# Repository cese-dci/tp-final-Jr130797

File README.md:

## Trabajo práctico final de la asignatura DCI ##

Este repositorio contiene el trabajo práctico final para la asignatura de Diseño de Circuitos Impresos de la carrera de posgrado de FIUBA.

* Autor: Ivan Vargas Marza 
* Título corto del trabajo:  Réplica de adaptador de amplificador Adafruit I2S Clase D
* Descripción: Se realiza la réplica del adaptador indicado, cambiando en modo mono del mismo a estéreo 

## Licencia de este trabajo ##

La licencia para este trabajo es la de Creative Commons Attribution-ShareAlike 4.0 International (CC BY-SA 4.0)

Se puede conocer más a detalle esta licencia en el siguiente enlace: https://creativecommons.org/licenses/by-sa/4.0/

## Estructura del TP FINAL ##

Toda la información pertinente a la réplica que se realizará se encuentra en: https://www.adafruit.com/product/3006

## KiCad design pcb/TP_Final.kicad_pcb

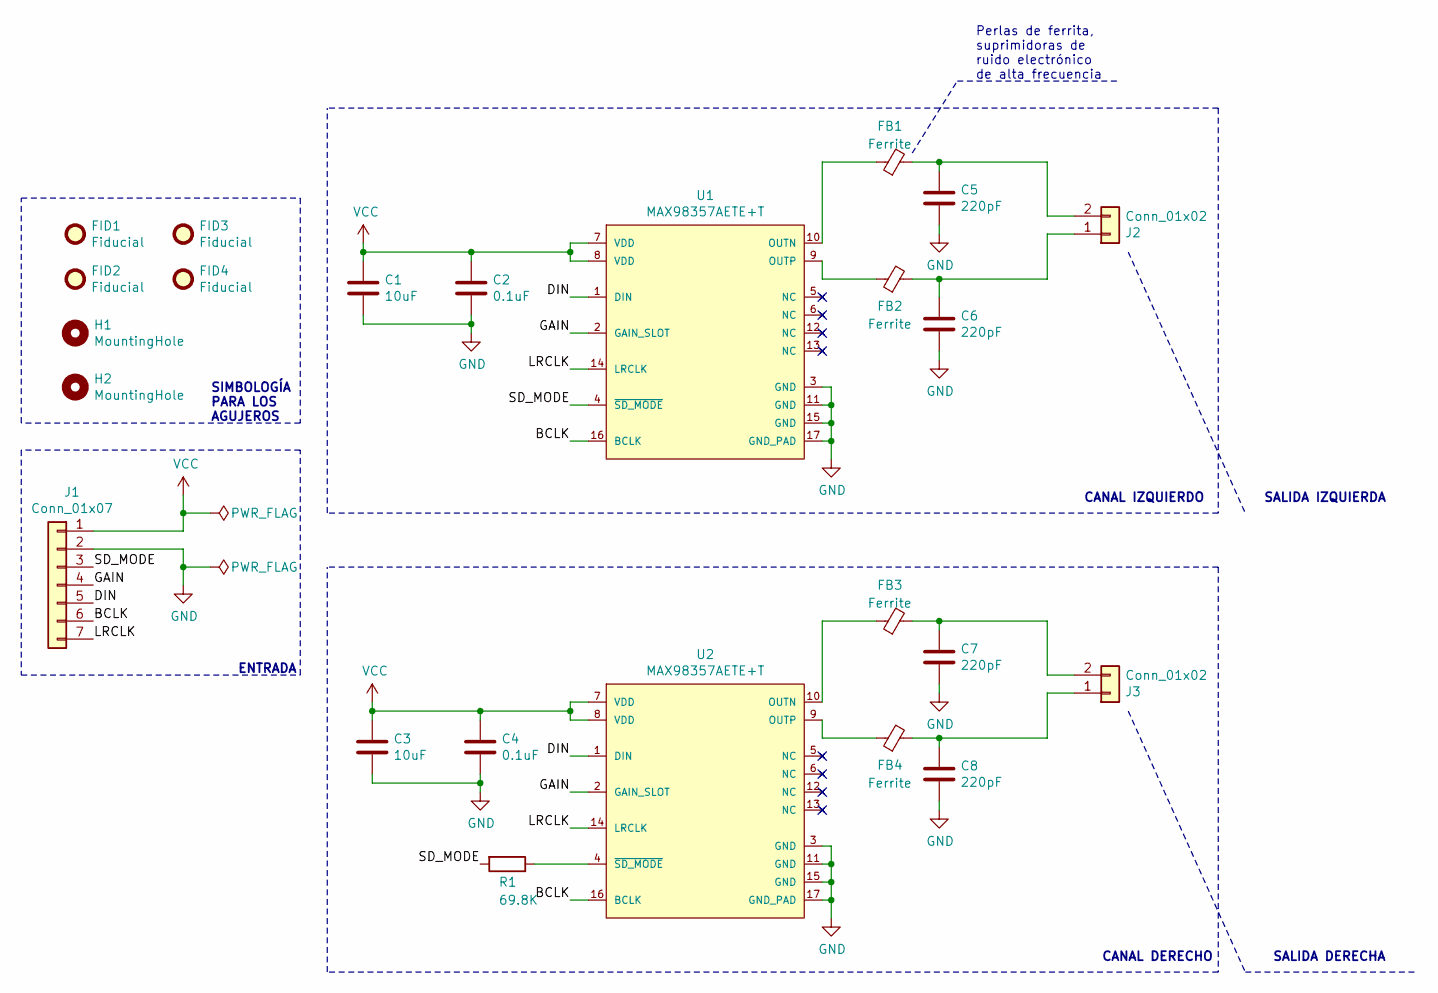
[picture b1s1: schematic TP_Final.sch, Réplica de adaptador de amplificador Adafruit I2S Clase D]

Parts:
C1, C3: 10uF; C_0805_2012Metric
C2, C4: 0.1uF; C_0805_2012Metric
C5, C6, C7, C8: 220pF; C_0805_2012Metric
FB1, FB2, FB3, FB4: Ferrite; Fuse_0805_2012Metric; digikey part number 710-742792030
FID1, FID2, FID3, FID4: Fiducial; Fiducial_0.5mm_Mask1mm
H1, H2: MountingHole; MountingHole_2mm
J1: Conn_01x07; PinHeader_1x07_P2.54mm_Vertical
J2, J3: Conn_01x02; TerminalBlock_Phoenix_MPT-0,5-2-2.54_1x02_P2.54mm_Horizontal
R1: 69.8K; R_0805_2012Metric; digikey description Resistores de alta frecuencia RF
U1, U2: MAX98357AETE+T; Maxim_Electronics-21-0896-0-0-0; mouser part number 700-MAX98357AETE+T; digikey description Amplifier IC 2-Channel (Stereo) Class D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

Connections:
/BCLK: J1.6, U1.16 (BCLK), U2.16 (BCLK)
/DIN: J1.5, U1.1 (DIN), U2.1 (DIN)
/GAIN: J1.4, U1.2 (GAIN_SLOT), U2.2 (GAIN_SLOT)
/LRCLK: J1.7, U1.14 (LRCLK), U2.14 (LRCLK)
/SD_MODE: J1.3, R1.2, U1.4 (~SD_MODE~)
GND: C1.2, C2.2, C3.2, C4.2, C5.2, C6.2, C7.2, C8.2, J1.2, U1.3 (GND), U1.11 (GND), U1.15 (GND), U1.17 (GND_PAD), U2.3 (GND), U2.11 (GND), U2.15 (GND), U2.17 (GND_PAD)
unnamed: C5.1, FB1.2, J2.2
unnamed: C6.1, FB2.2, J2.1
unnamed: C7.1, FB3.2, J3.2
unnamed: C8.1, FB4.2, J3.1
unnamed: FB1.1, U1.10 (OUTN)
unnamed: FB2.1, U1.9 (OUTP)
unnamed: FB3.1, U2.10 (OUTN)
unnamed: FB4.1, U2.9 (OUTP)
unnamed: R1.1, U2.4 (~SD_MODE~)
VCC: C1.1, C2.1, C3.1, C4.1, J1.1, U1.7 (VDD), U1.8 (VDD), U2.7 (VDD), U2.8 (VDD)

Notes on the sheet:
CANAL IZQUIERDO
CANAL DERECHO
ENTRADA
SALIDA IZQUIERDA
SALIDA DERECHA
Perlas de ferrita, suprimidoras de ruido electrónico de alta frecuencia
SIMBOLOGÍA PARA LOS AGUJEROS

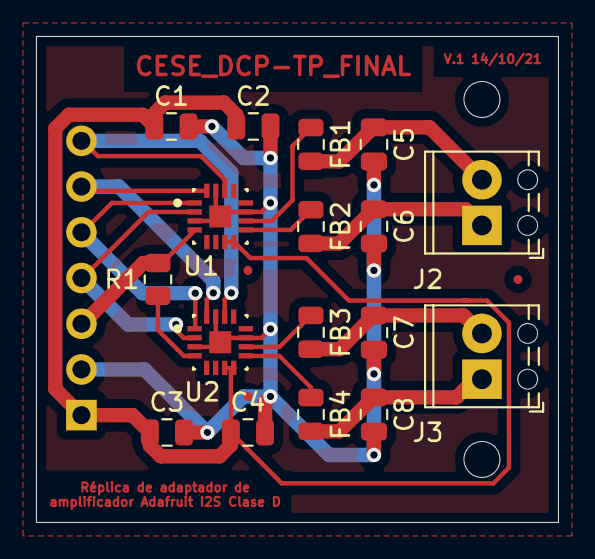
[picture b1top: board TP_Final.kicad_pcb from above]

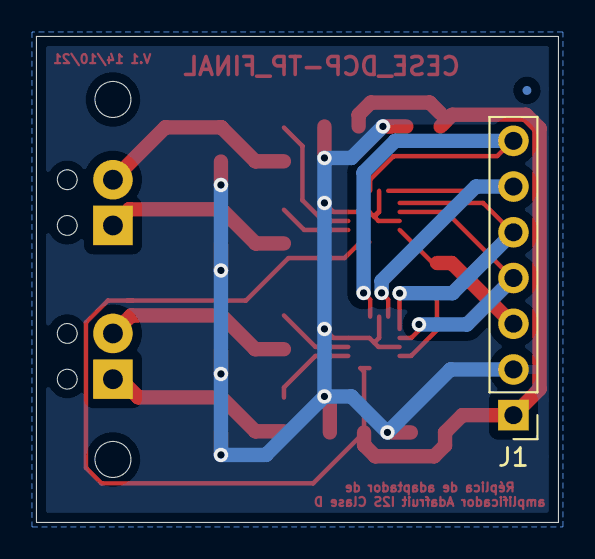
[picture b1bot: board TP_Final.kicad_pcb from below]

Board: 2 copper layers, 29.0 x 27.0 mm, 24 parts (2 on the bottom side), 16 nets.

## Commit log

2021-09-09 Esquemático
2021-09-23 Esquemático y Asociaciones
2021-10-14 Modelos 3D y PCB
2021-10-15 Correciones

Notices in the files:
pcb/TP_Final.kicad_pcb:
Creative Commons License
